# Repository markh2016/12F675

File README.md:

# 12F675
Simple  starter  XC8 program to flash led using XC8 compiler and  pickit3
included all data sheets for pic12f675 and mpsa42  npn transistor 
The zener diode  you can use any 5.6volt zener but make sure its rated at 1300mw 
Kicad poroject folder  with schematic and PCB layout 
Bill of matarials in csv format 

The board layout for you  using blackboard mpu  available from git hub at this address https://github.com/mpue/blackboard

You will also need MPLABX ide for this

Link below
https://www.microchip.com/en-us/tools-resources/develop/mplab-x-ide

Plus the XC8 , XC16 compilers

https://www.microchip.com/en-us/tools-resources/develop/mplab-xc-compilers

Dont forget to install the MLAB IPE otherwise you wont be able to blow the chip

If you need Kicad most Linux distro's ship with this but you can download this from here at this link

https://www.kicad.org/download/linux/

Finally if you want to make a casing of sorts for this then try free-cad

Here is the link for doing this

https://www.freecad.org/downloads.php

Couldnt think of anything else you need plus there is the full xc8 project files and diagrams for connecting pickit-3 
Instructions for this are nicley detailed on this site 

https://alselectro.wordpress.com/2020/06/25/getting-started-with-programming-pic-12f675

Enjoy !!

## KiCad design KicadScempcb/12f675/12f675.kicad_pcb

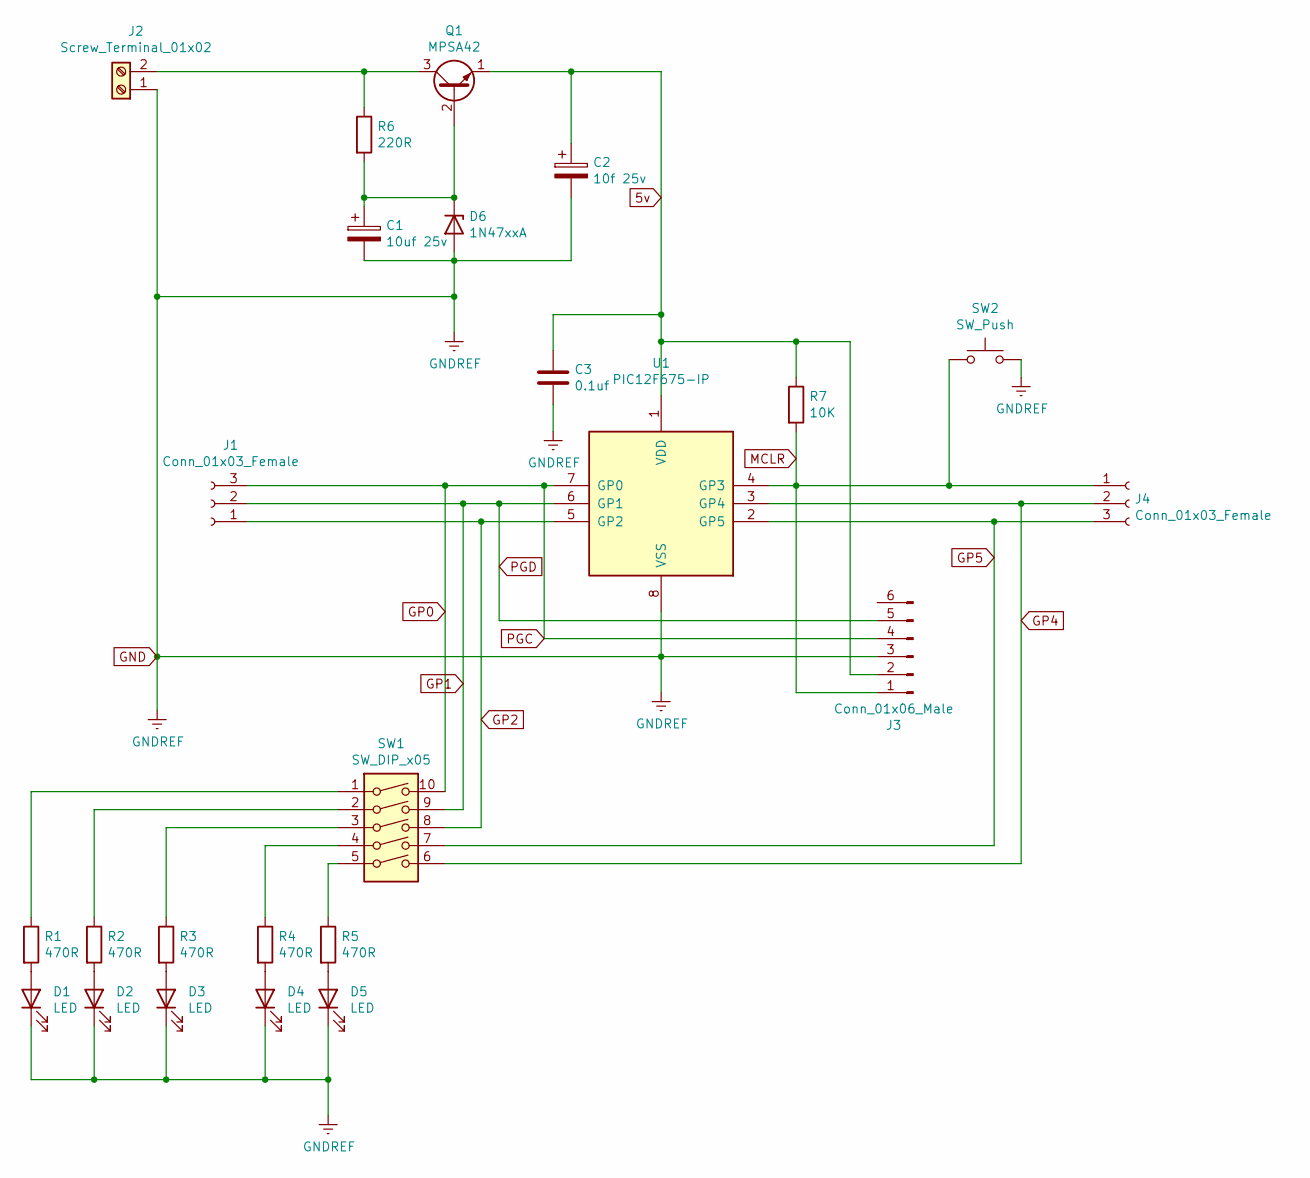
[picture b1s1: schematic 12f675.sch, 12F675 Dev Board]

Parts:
C1: 10uf 25v; CP_Radial_D4.0mm_P2.00mm
C2: 10f 25v; CP_Radial_D4.0mm_P2.00mm
C3: 0.1uf; C_Disc_D4.3mm_W1.9mm_P5.00mm
D1, D2, D3, D4, D5: LED; LED_D5.0mm
D6: 1N47xxA; D_DO-41_SOD81_P10.16mm_Horizontal
J1, J4: Conn_01x03_Female; PinHeader_1x03_P2.00mm_Vertical
J2: Screw_Terminal_01x02; TerminalBlock_4Ucon_1x02_P3.50mm_Horizontal
J3: Conn_01x06_Male; PinHeader_1x06_P2.00mm_Vertical
Q1: MPSA42; TO-92_Inline
R1, R2, R3, R4, R5: 470R; R_Axial_DIN0207_L6.3mm_D2.5mm_P10.16mm_Horizontal
R6: 220R; R_Axial_DIN0207_L6.3mm_D2.5mm_P10.16mm_Horizontal
R7: 10K; R_Axial_DIN0207_L6.3mm_D2.5mm_P10.16mm_Horizontal
SW1: SW_DIP_x05; SW_DIP_SPSTx05_Slide_6.7x14.26mm_W7.62mm_P2.54mm_LowProfile
SW2: SW_Push; SW_Tactile_Straight_KSL0Axx1LFTR
U1: PIC12F675-IP; DIP-8_W7.62mm

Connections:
5v: C2.1, C3.1, J3.2, Q1.1 (E), R7.1, U1.1 (VDD)
GND: C1.2, C2.2, C3.2, D1.1 (K), D2.1 (K), D3.1 (K), D4.1 (K), D5.1 (K), D6.2 (A), J2.1, J3.3, SW2.2, U1.8 (VSS)
GP0: J1.3, J3.4, SW1.10, U1.7 (GP0)
GP1: J1.2, J3.5, SW1.9, U1.6 (GP1)
GP2: J1.1, SW1.8, U1.5 (GP2)
GP4: J4.2, SW1.6, U1.3 (GP4)
GP5: J4.3, SW1.7, U1.2 (GP5)
MCLR: J3.1, J4.1, R7.2, SW2.1, U1.4 (GP3)
unnamed: C1.1, D6.1 (K), Q1.2 (B), R6.2
unnamed: D1.2 (A), R1.2
unnamed: D2.2 (A), R2.2
unnamed: D3.2 (A), R3.2
unnamed: D4.2 (A), R4.2
unnamed: D5.2 (A), R5.2
unnamed: J2.2, Q1.3 (C), R6.1
unnamed: R1.1, SW1.1
unnamed: R2.1, SW1.2
unnamed: R3.1, SW1.3
unnamed: R4.1, SW1.4
unnamed: R5.1, SW1.5

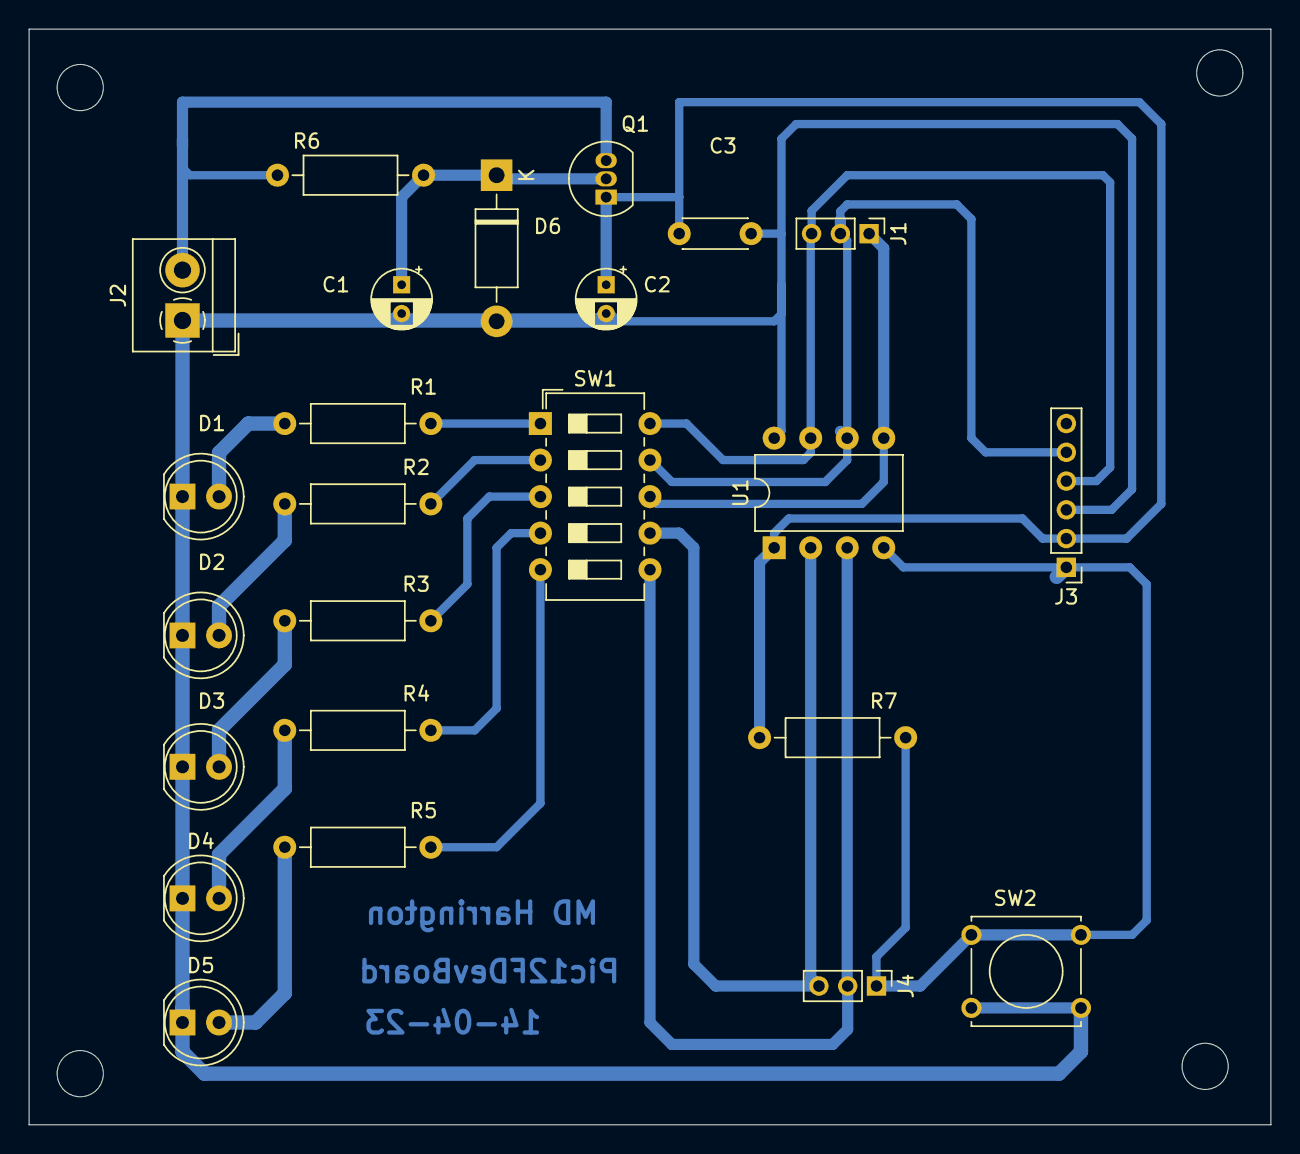
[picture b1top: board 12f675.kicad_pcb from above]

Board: 2 copper layers, 86.4 x 76.2 mm, 24 parts (0 on the bottom side), 20 nets.

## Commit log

2023-04-12 Add files via upload
    Added image plus bb file using Java open source https://github.com/mpue/blackboard
2023-04-12 Add files via upload
    Mistake made on GND of IC ab
2023-04-12 Add files via upload
    added pic3 programmer to show connections and how to use
    https://alselectro.wordpress.com/2020/06/25/getting-started-with-programming-pic-12f675/
2023-04-12 Added changed bb file , pdf datasheets for mpsa 42
2023-04-12 Now included Kicad design files
2023-04-12 Updated readme files to reflect links needed
